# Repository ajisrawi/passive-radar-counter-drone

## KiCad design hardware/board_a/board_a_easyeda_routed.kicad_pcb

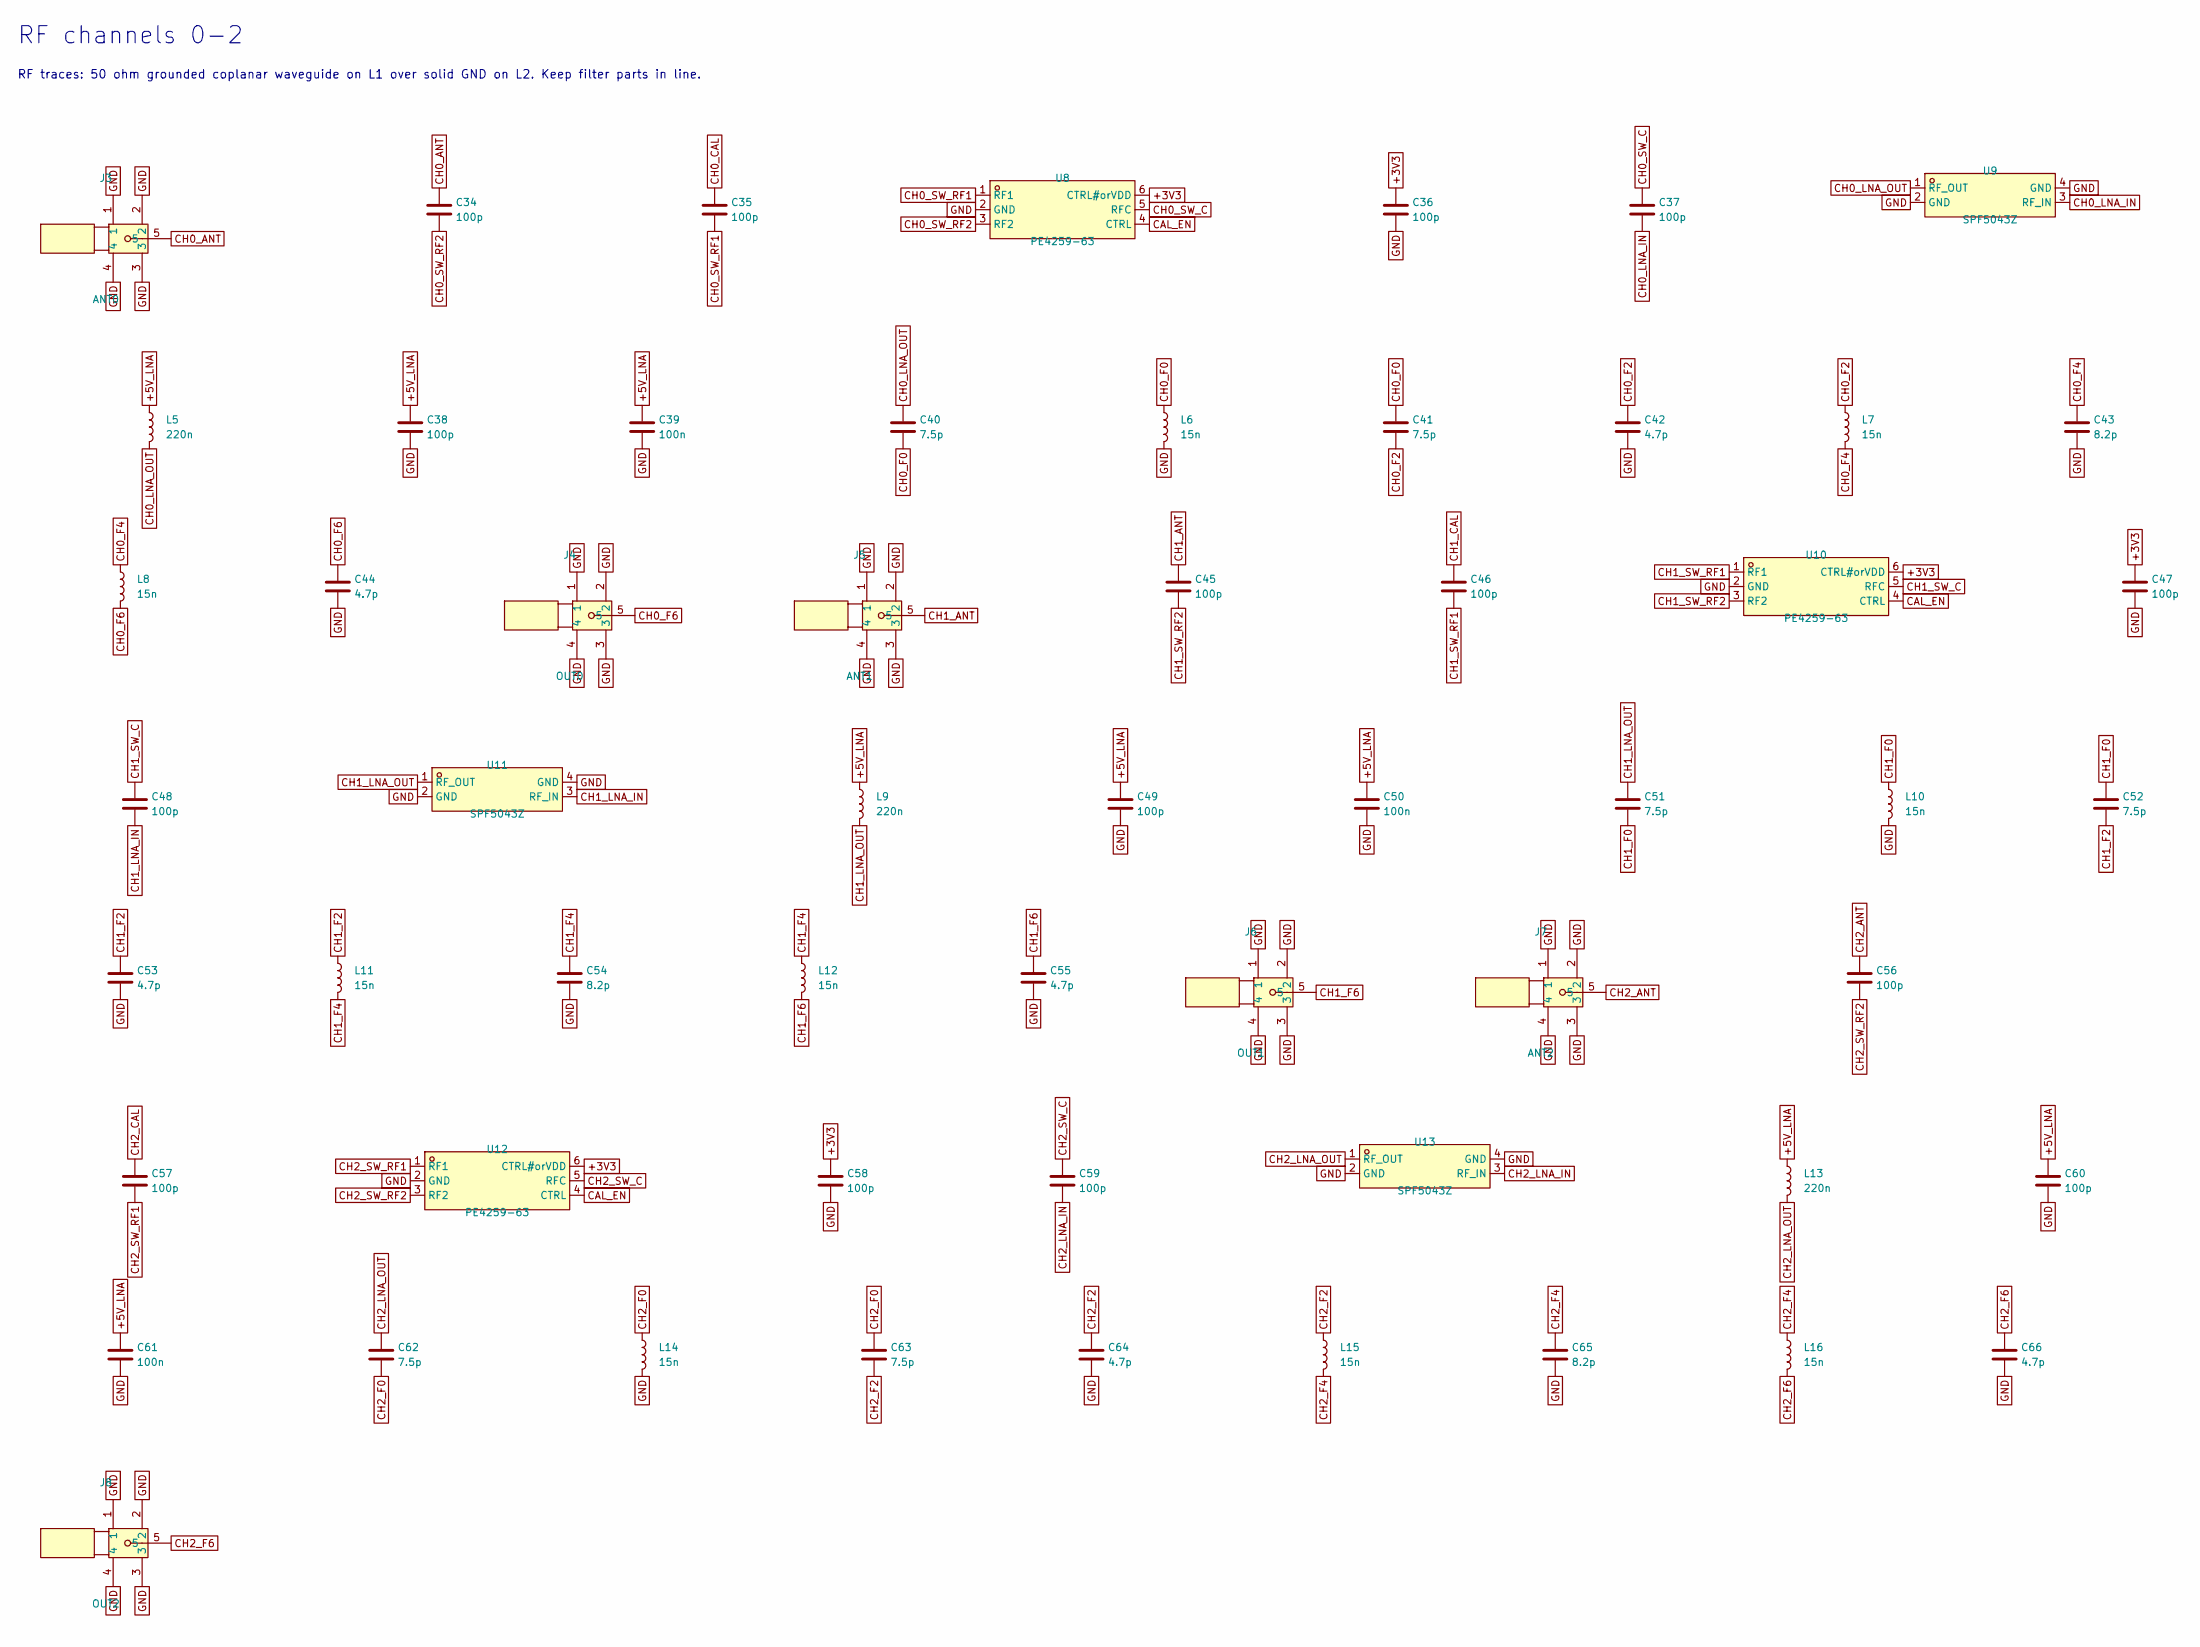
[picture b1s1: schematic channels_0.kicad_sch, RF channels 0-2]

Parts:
C34, C35, C36, C37, C38, C45, C46, C47, C48, C49, C56, C57, C58, C59, C60: 100p; C_0402_1005Metric
C39, C50, C61: 100n; C_0402_1005Metric; LCSC C1525
C40, C41, C51, C52, C62, C63: 7.5p; C_0402_1005Metric
C42, C44, C53, C55, C64, C66: 4.7p; C_0402_1005Metric
C43, C54, C65: 8.2p; C_0402_1005Metric
J3: ANT0; SMA-TH_BWSMA-KE-Z001; MPN BWSMA-KE-Z001; LCSC C496549
J4: OUT0; SMA-TH_BWSMA-KE-Z001; MPN BWSMA-KE-Z001; LCSC C496549
J5: ANT1; SMA-TH_BWSMA-KE-Z001; MPN BWSMA-KE-Z001; LCSC C496549
J6: OUT1; SMA-TH_BWSMA-KE-Z001; MPN BWSMA-KE-Z001; LCSC C496549
J7: ANT2; SMA-TH_BWSMA-KE-Z001; MPN BWSMA-KE-Z001; LCSC C496549
J8: OUT2; SMA-TH_BWSMA-KE-Z001; MPN BWSMA-KE-Z001; LCSC C496549
L5, L9, L13: 220n; L_0603_1608Metric
L6, L7, L8, L10, L11, L12, L14, L15, L16: 15n; L_0402_1005Metric
U8, U10, U12: PE4259-63; SC-70-6_L2.2-W1.3-P0.65-LS2.1-BL; MPN PE4259-63; LCSC C470892
U9, U11, U13: SPF5043Z; SOT343_L2.0-W1.3-P1.30-LS2.1-BL; MPN SPF5043Z; LCSC C470902

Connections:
+3V3: C36.1, C47.1, C58.1, U8.6 (CTRL#orVDD), U10.6 (CTRL#orVDD), U12.6 (CTRL#orVDD); also elsewhere on the board
+5V_LNA: C38.1, C39.1, C49.1, C50.1, C60.1, C61.1, L5.1, L9.1, L13.1; also elsewhere on the board
CAL_EN: U8.4 (CTRL), U10.4 (CTRL), U12.4 (CTRL); also elsewhere on the board
CH0_ANT: C34.1, J3.5
CH0_CAL: C35.1; also elsewhere on the board
CH0_F0: C40.2, C41.1, L6.1
CH0_F2: C41.2, C42.1, L7.1
CH0_F4: C43.1, L7.2, L8.1
CH0_F6: C44.1, J4.5, L8.2
CH0_LNA_IN: C37.2, U9.3 (RF_IN)
CH0_LNA_OUT: C40.1, L5.2, U9.1 (RF_OUT)
CH0_SW_C: C37.1, U8.5 (RFC)
CH0_SW_RF1: C35.2, U8.1 (RF1)
CH0_SW_RF2: C34.2, U8.3 (RF2)
CH1_ANT: C45.1, J5.5
CH1_CAL: C46.1; also elsewhere on the board
CH1_F0: C51.2, C52.1, L10.1
CH1_F2: C52.2, C53.1, L11.1
CH1_F4: C54.1, L11.2, L12.1
CH1_F6: C55.1, J6.5, L12.2
CH1_LNA_IN: C48.2, U11.3 (RF_IN)
CH1_LNA_OUT: C51.1, L9.2, U11.1 (RF_OUT)
CH1_SW_C: C48.1, U10.5 (RFC)
CH1_SW_RF1: C46.2, U10.1 (RF1)
CH1_SW_RF2: C45.2, U10.3 (RF2)
CH2_ANT: C56.1, J7.5
CH2_CAL: C57.1; also elsewhere on the board
CH2_F0: C62.2, C63.1, L14.1
CH2_F2: C63.2, C64.1, L15.1
CH2_F4: C65.1, L15.2, L16.1
CH2_F6: C66.1, J8.5, L16.2
CH2_LNA_IN: C59.2, U13.3 (RF_IN)
CH2_LNA_OUT: C62.1, L13.2, U13.1 (RF_OUT)
CH2_SW_C: C59.1, U12.5 (RFC)
CH2_SW_RF1: C57.2, U12.1 (RF1)
CH2_SW_RF2: C56.2, U12.3 (RF2)
GND: C36.2, C38.2, C39.2, C42.2, C43.2, C44.2, C47.2, C49.2, C50.2, C53.2, C54.2, C55.2, C58.2, C60.2, C61.2, C64.2, C65.2, C66.2, J3.1, J3.2, J3.3, J3.4, J4.1, J4.2, J4.3, J4.4, J5.1, J5.2, J5.3, J5.4, J6.1, J6.2, J6.3, J6.4, J7.1, J7.2, J7.3, J7.4, J8.1, J8.2, J8.3, J8.4, L6.2, L10.2, L14.2, U8.2 (GND), U9.2 (GND), U9.4 (GND), U10.2 (GND), U11.2 (GND), U11.4 (GND), U12.2 (GND), U13.2 (GND), U13.4 (GND); also elsewhere on the board

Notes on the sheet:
RF channels 0-2
RF traces: 50 ohm grounded coplanar waveguide on L1 over solid GND on L2. Keep filter parts in line.

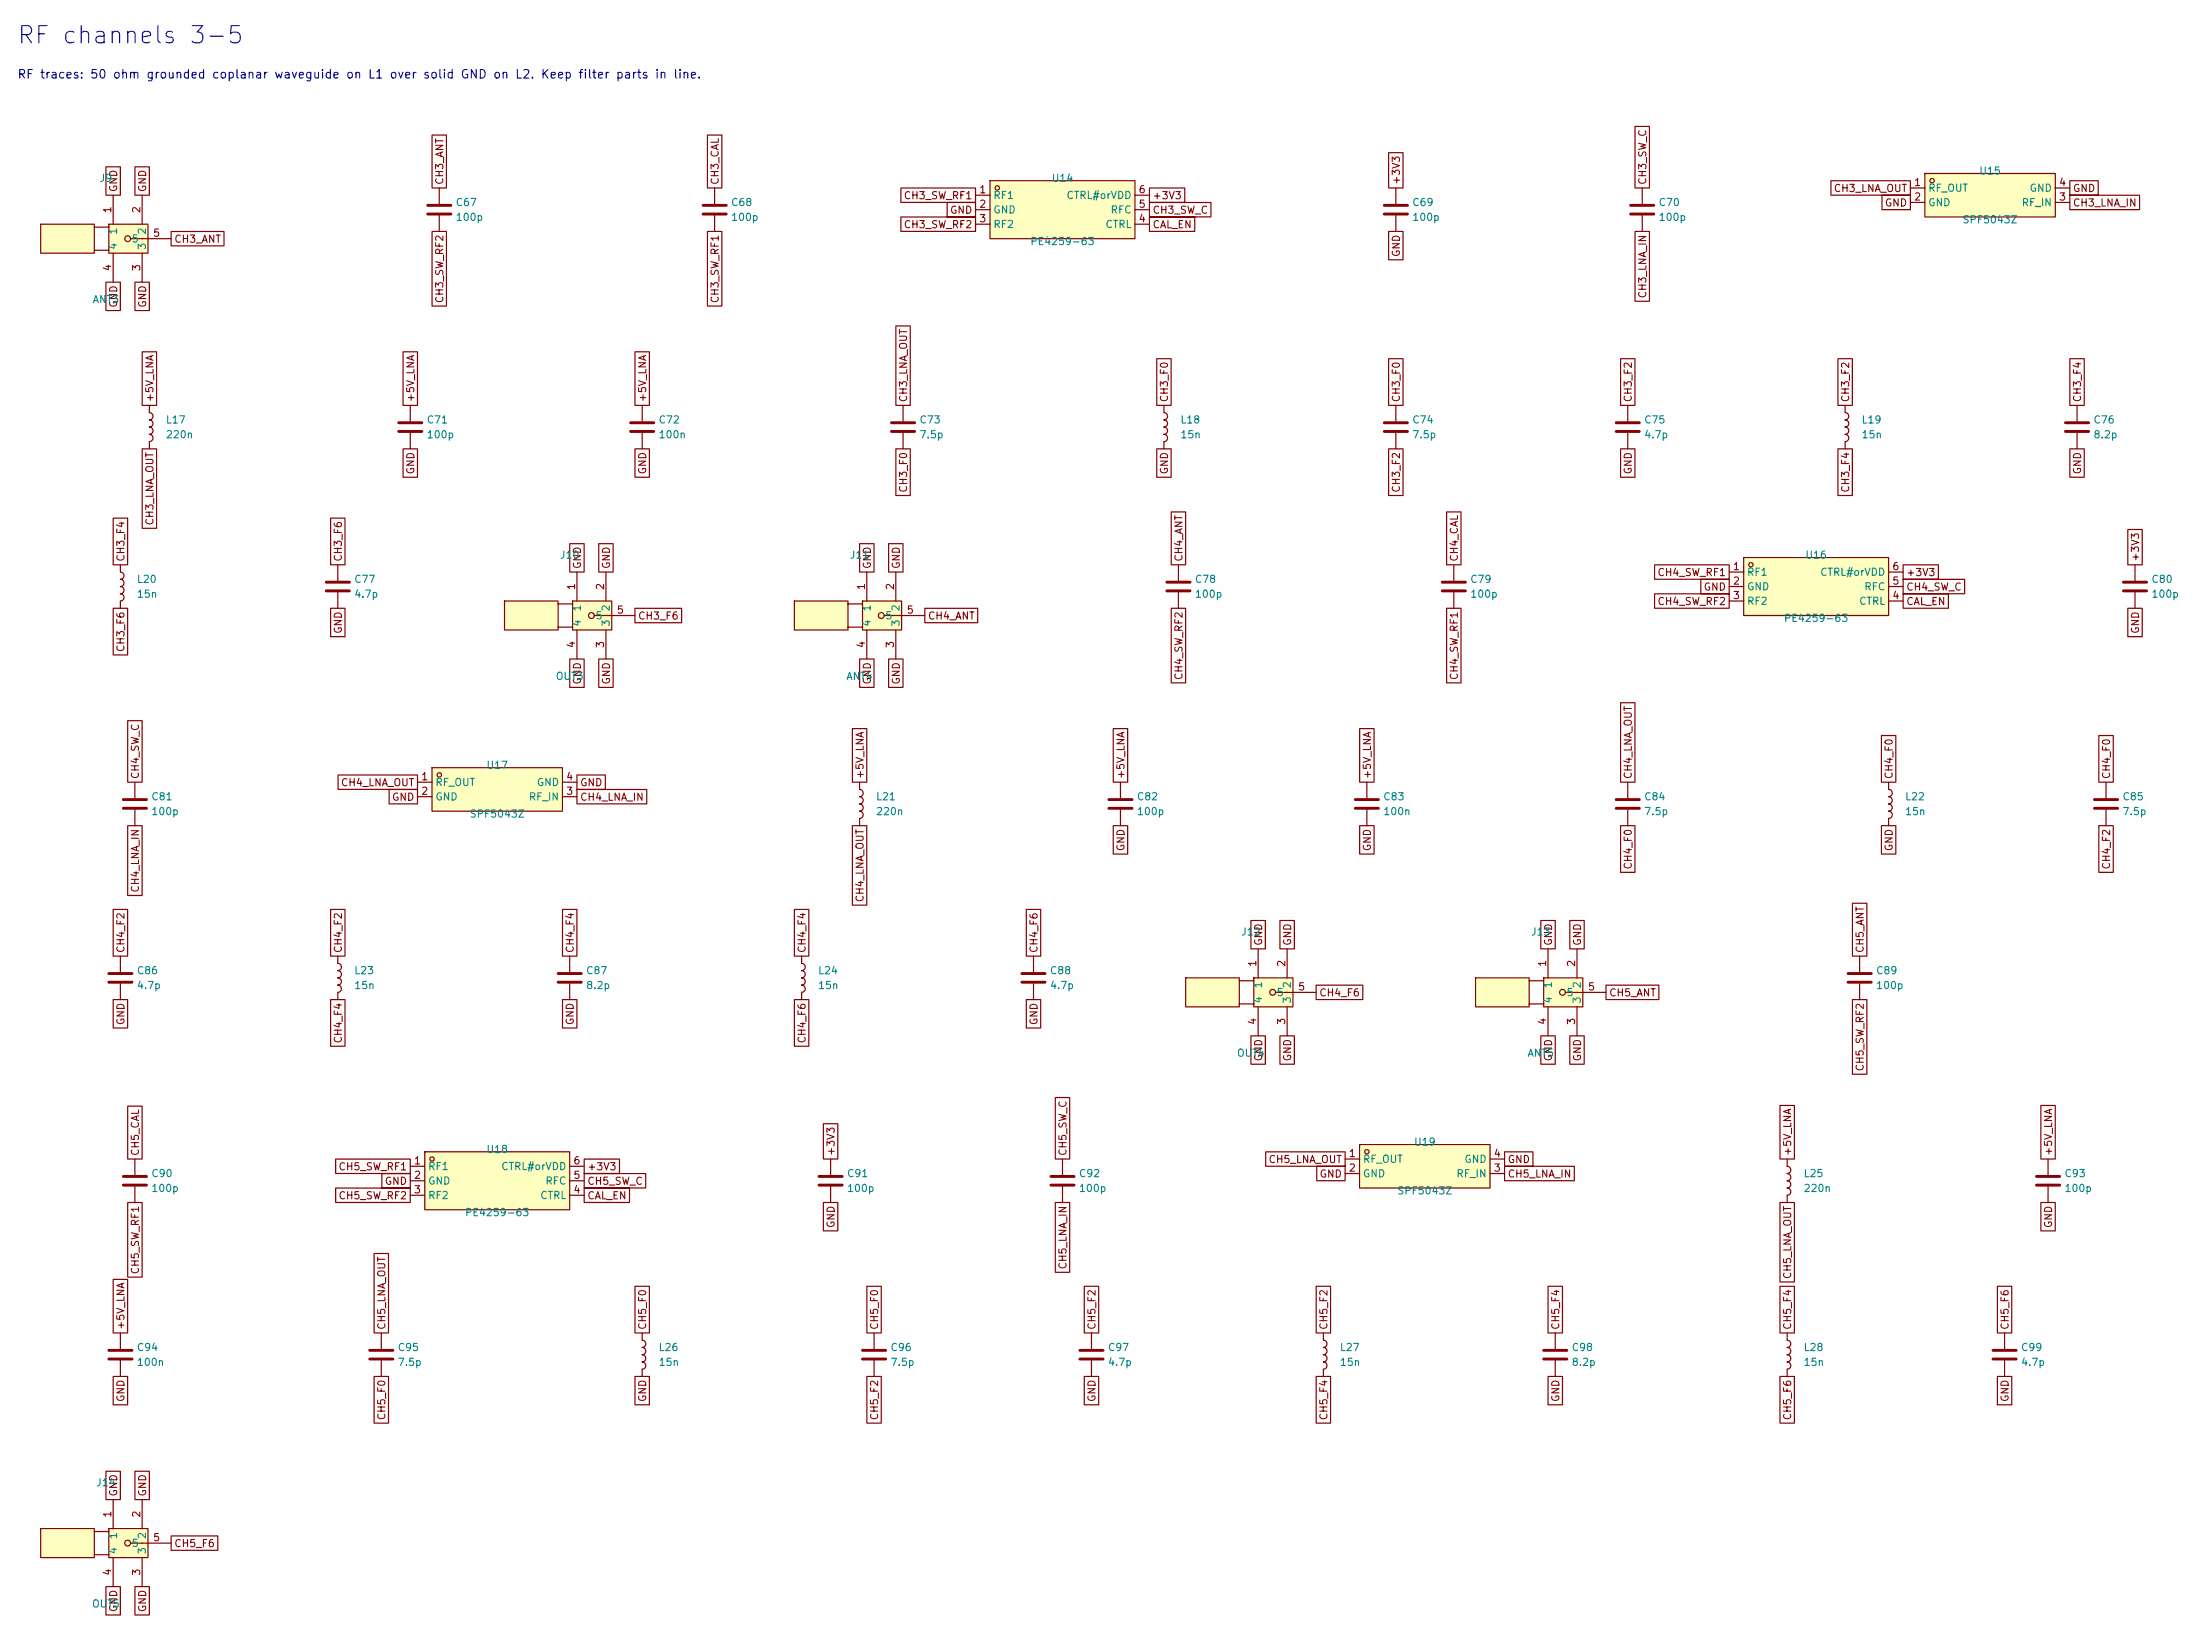
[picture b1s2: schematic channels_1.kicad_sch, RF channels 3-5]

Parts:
C67, C68, C69, C70, C71, C78, C79, C80, C81, C82, C89, C90, C91, C92, C93: 100p; C_0402_1005Metric
C72, C83, C94: 100n; C_0402_1005Metric; LCSC C1525
C73, C74, C84, C85, C95, C96: 7.5p; C_0402_1005Metric
C75, C77, C86, C88, C97, C99: 4.7p; C_0402_1005Metric
C76, C87, C98: 8.2p; C_0402_1005Metric
J9: ANT3; SMA-TH_BWSMA-KE-Z001; MPN BWSMA-KE-Z001; LCSC C496549
J10: OUT3; SMA-TH_BWSMA-KE-Z001; MPN BWSMA-KE-Z001; LCSC C496549
J11: ANT4; SMA-TH_BWSMA-KE-Z001; MPN BWSMA-KE-Z001; LCSC C496549
J12: OUT4; SMA-TH_BWSMA-KE-Z001; MPN BWSMA-KE-Z001; LCSC C496549
J13: ANT5; SMA-TH_BWSMA-KE-Z001; MPN BWSMA-KE-Z001; LCSC C496549
J14: OUT5; SMA-TH_BWSMA-KE-Z001; MPN BWSMA-KE-Z001; LCSC C496549
L17, L21, L25: 220n; L_0603_1608Metric
L18, L19, L20, L22, L23, L24, L26, L27, L28: 15n; L_0402_1005Metric
U14, U16, U18: PE4259-63; SC-70-6_L2.2-W1.3-P0.65-LS2.1-BL; MPN PE4259-63; LCSC C470892
U15, U17, U19: SPF5043Z; SOT343_L2.0-W1.3-P1.30-LS2.1-BL; MPN SPF5043Z; LCSC C470902

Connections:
+3V3: C69.1, C80.1, C91.1, U14.6 (CTRL#orVDD), U16.6 (CTRL#orVDD), U18.6 (CTRL#orVDD); also elsewhere on the board
+5V_LNA: C71.1, C72.1, C82.1, C83.1, C93.1, C94.1, L17.1, L21.1, L25.1; also elsewhere on the board
CAL_EN: U14.4 (CTRL), U16.4 (CTRL), U18.4 (CTRL); also elsewhere on the board
CH3_ANT: C67.1, J9.5
CH3_CAL: C68.1; also elsewhere on the board
CH3_F0: C73.2, C74.1, L18.1
CH3_F2: C74.2, C75.1, L19.1
CH3_F4: C76.1, L19.2, L20.1
CH3_F6: C77.1, J10.5, L20.2
CH3_LNA_IN: C70.2, U15.3 (RF_IN)
CH3_LNA_OUT: C73.1, L17.2, U15.1 (RF_OUT)
CH3_SW_C: C70.1, U14.5 (RFC)
CH3_SW_RF1: C68.2, U14.1 (RF1)
CH3_SW_RF2: C67.2, U14.3 (RF2)
CH4_ANT: C78.1, J11.5
CH4_CAL: C79.1; also elsewhere on the board
CH4_F0: C84.2, C85.1, L22.1
CH4_F2: C85.2, C86.1, L23.1
CH4_F4: C87.1, L23.2, L24.1
CH4_F6: C88.1, J12.5, L24.2
CH4_LNA_IN: C81.2, U17.3 (RF_IN)
CH4_LNA_OUT: C84.1, L21.2, U17.1 (RF_OUT)
CH4_SW_C: C81.1, U16.5 (RFC)
CH4_SW_RF1: C79.2, U16.1 (RF1)
CH4_SW_RF2: C78.2, U16.3 (RF2)
CH5_ANT: C89.1, J13.5
CH5_CAL: C90.1; also elsewhere on the board
CH5_F0: C95.2, C96.1, L26.1
CH5_F2: C96.2, C97.1, L27.1
CH5_F4: C98.1, L27.2, L28.1
CH5_F6: C99.1, J14.5, L28.2
CH5_LNA_IN: C92.2, U19.3 (RF_IN)
CH5_LNA_OUT: C95.1, L25.2, U19.1 (RF_OUT)
CH5_SW_C: C92.1, U18.5 (RFC)
CH5_SW_RF1: C90.2, U18.1 (RF1)
CH5_SW_RF2: C89.2, U18.3 (RF2)
GND: C69.2, C71.2, C72.2, C75.2, C76.2, C77.2, C80.2, C82.2, C83.2, C86.2, C87.2, C88.2, C91.2, C93.2, C94.2, C97.2, C98.2, C99.2, J9.1, J9.2, J9.3, J9.4, J10.1, J10.2, J10.3, J10.4, J11.1, J11.2, J11.3, J11.4, J12.1, J12.2, J12.3, J12.4, J13.1, J13.2, J13.3, J13.4, J14.1, J14.2, J14.3, J14.4, L18.2, L22.2, L26.2, U14.2 (GND), U15.2 (GND), U15.4 (GND), U16.2 (GND), U17.2 (GND), U17.4 (GND), U18.2 (GND), U19.2 (GND), U19.4 (GND); also elsewhere on the board

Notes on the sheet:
RF channels 3-5
RF traces: 50 ohm grounded coplanar waveguide on L1 over solid GND on L2. Keep filter parts in line.

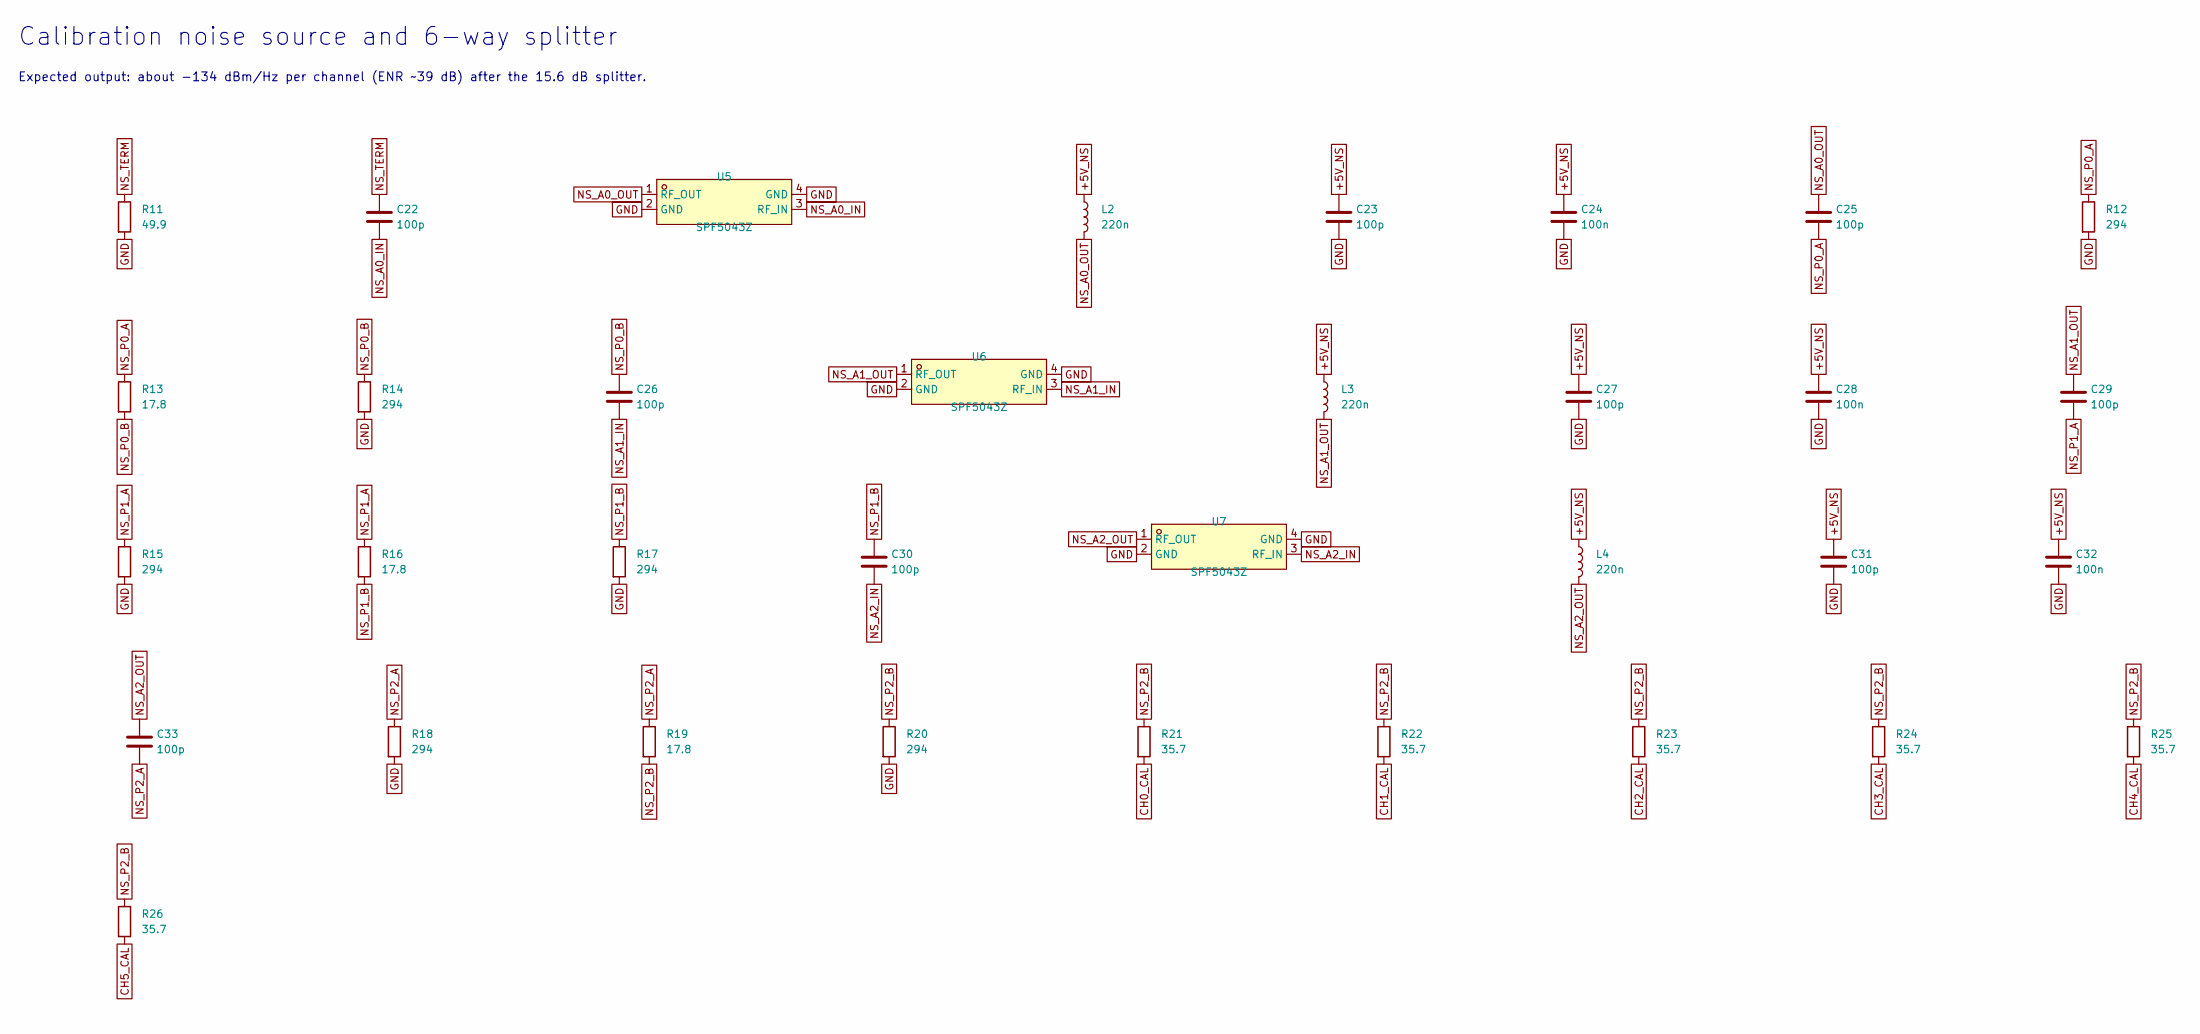
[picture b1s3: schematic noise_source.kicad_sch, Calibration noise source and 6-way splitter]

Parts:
C22, C23, C25, C26, C27, C29, C30, C31, C33: 100p; C_0402_1005Metric
C24, C28, C32: 100n; C_0402_1005Metric; LCSC C1525
L2, L3, L4: 220n; L_0603_1608Metric
R11: 49.9; R_0402_1005Metric
R12, R14, R15, R17, R18, R20: 294; R_0402_1005Metric
R13, R16, R19: 17.8; R_0402_1005Metric
R21, R22, R23, R24, R25, R26: 35.7; R_0402_1005Metric
U5, U6, U7: SPF5043Z; SOT343_L2.0-W1.3-P1.30-LS2.1-BL; MPN SPF5043Z; LCSC C470902

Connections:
+5V_NS: C23.1, C24.1, C27.1, C28.1, C31.1, C32.1, L2.1, L3.1, L4.1; also elsewhere on the board
CH0_CAL: R21.2; also elsewhere on the board
CH1_CAL: R22.2; also elsewhere on the board
CH2_CAL: R23.2; also elsewhere on the board
CH3_CAL: R24.2; also elsewhere on the board
CH4_CAL: R25.2; also elsewhere on the board
CH5_CAL: R26.2; also elsewhere on the board
GND: C23.2, C24.2, C27.2, C28.2, C31.2, C32.2, R11.2, R12.2, R14.2, R15.2, R17.2, R18.2, R20.2, U5.2 (GND), U5.4 (GND), U6.2 (GND), U6.4 (GND), U7.2 (GND), U7.4 (GND); also elsewhere on the board
NS_A0_IN: C22.2, U5.3 (RF_IN)
NS_A0_OUT: C25.1, L2.2, U5.1 (RF_OUT)
NS_A1_IN: C26.2, U6.3 (RF_IN)
NS_A1_OUT: C29.1, L3.2, U6.1 (RF_OUT)
NS_A2_IN: C30.2, U7.3 (RF_IN)
NS_A2_OUT: C33.1, L4.2, U7.1 (RF_OUT)
NS_P0_A: C25.2, R12.1, R13.1
NS_P0_B: C26.1, R13.2, R14.1
NS_P1_A: C29.2, R15.1, R16.1
NS_P1_B: C30.1, R16.2, R17.1
NS_P2_A: C33.2, R18.1, R19.1
NS_P2_B: R19.2, R20.1, R21.1, R22.1, R23.1, R24.1, R25.1, R26.1
NS_TERM: C22.1, R11.1

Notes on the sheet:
Calibration noise source and 6-way splitter
Expected output: about -134 dBm/Hz per channel (ENR ~39 dB) after the 15.6 dB splitter.

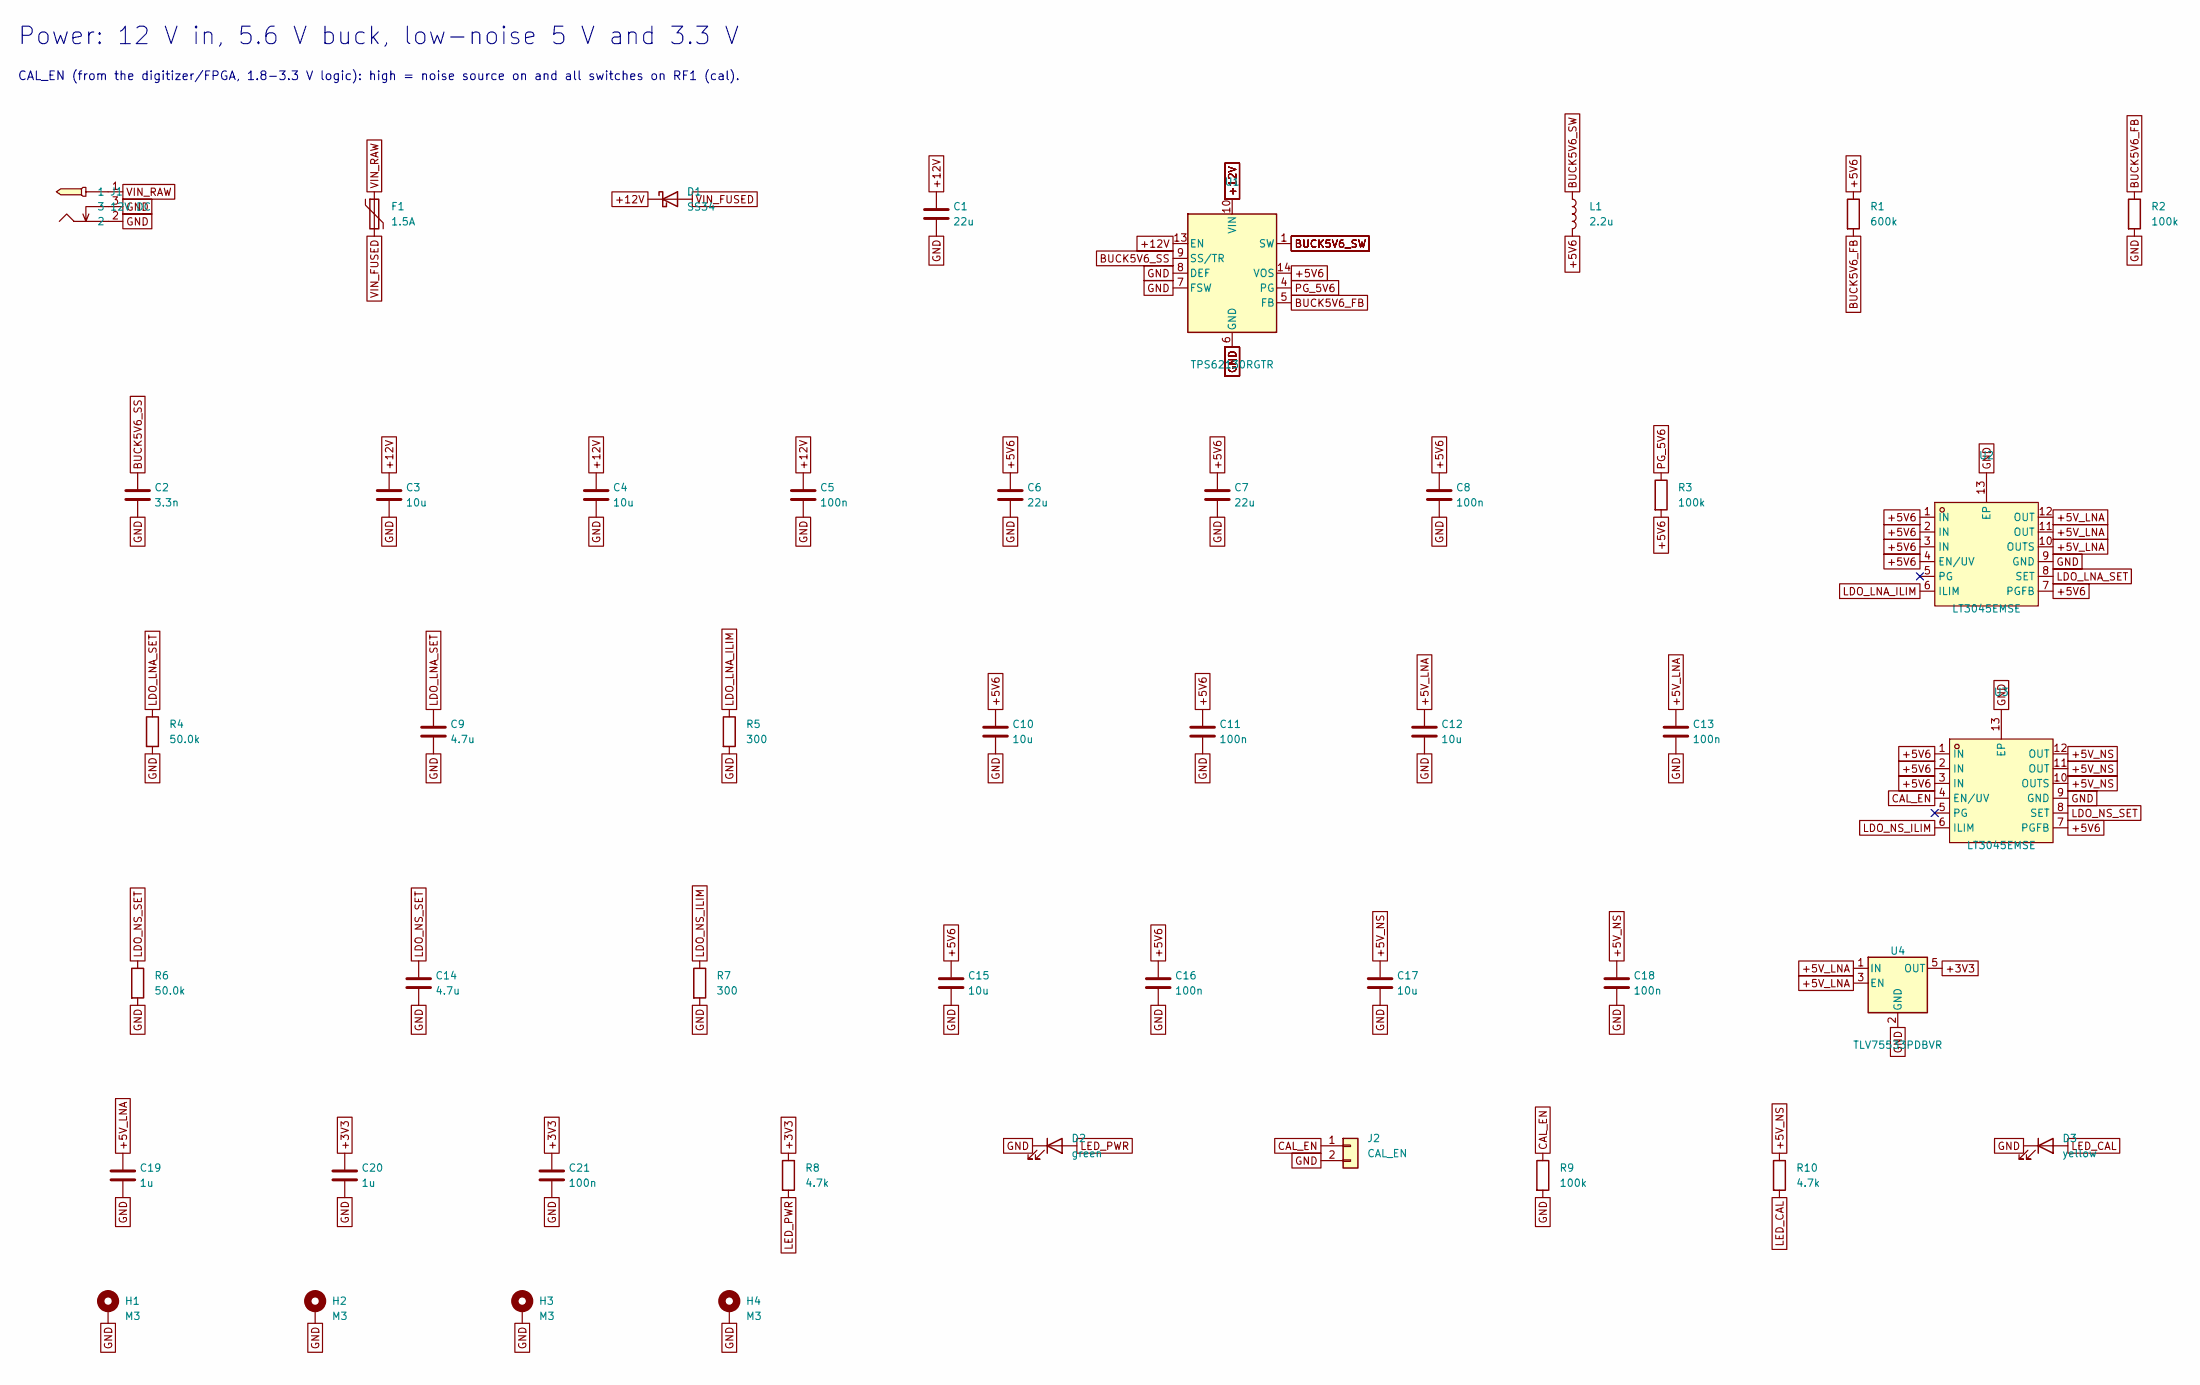
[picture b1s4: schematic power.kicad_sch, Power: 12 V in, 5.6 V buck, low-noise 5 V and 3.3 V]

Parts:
C1: 22u; C_1206_3216Metric
C2: 3.3n; C_0402_1005Metric
C3, C4: 10u; C_0805_2012Metric
C5, C8, C11, C13, C16, C18, C21: 100n; C_0402_1005Metric; LCSC C1525
C6, C7: 22u; C_0805_2012Metric; LCSC C45783
C9, C14: 4.7u; C_0603_1608Metric
C10, C12, C15, C17: 10u; C_0603_1608Metric; LCSC C19702
C19, C20: 1u; C_0402_1005Metric; LCSC C52923
D1: SS34; D_SMA; MPN SS34; LCSC C8678
D2: green; LED_0603_1608Metric
D3: yellow; LED_0603_1608Metric
F1: 1.5A; Fuse_1206_3216Metric
H1, H2, H3, H4: M3; MountingHole_3.2mm_M3_Pad_Via
J1: 12V DC; DC-IN-TH_DC-005C-20A; MPN DC-005C-20A; LCSC C84007
J2: CAL_EN; PinHeader_1x02_P2.54mm_Vertical
L1: 2.2u; L_Bourns-SRN4018; MPN SRN4018-2R2M
R1: 600k; R_0402_1005Metric
R2, R3, R9: 100k; R_0402_1005Metric; LCSC C25741
R4, R6: 50.0k; R_0402_1005Metric; Tolerance 0.1%
R5, R7: 300; R_0402_1005Metric
R8, R10: 4.7k; R_0402_1005Metric; LCSC C25900
U1: TPS62130RGTR; VQFN-16-1EP_3x3mm_P0.5mm_EP1.68x1.68mm; MPN TPS62130RGTR; LCSC C43590
U2, U3: LT3045EMSE; MSOP-12_L4.0-W3.0-P0.65-LS4.9-BL-EP; MPN LT3045EMSE#PBF; LCSC C580012
U4: TLV75533PDBVR; SOT-23-5; LCSC C404027

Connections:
+3V3: C20.1, C21.1, R8.1, U4.5 (OUT); also elsewhere on the board
+5V6: C6.1, C7.1, C8.1, C10.1, C11.1, C15.1, C16.1, L1.2, R1.1, R3.2, U1.14 (VOS), U2.1 (IN), U2.2 (IN), U2.3 (IN), U2.4 (EN/UV), U2.7 (PGFB), U3.1 (IN), U3.2 (IN), U3.3 (IN), U3.7 (PGFB)
+5V_LNA: C12.1, C13.1, C19.1, U2.10 (OUTS), U2.11 (OUT), U2.12 (OUT), U4.1 (IN), U4.3 (EN); also elsewhere on the board
+5V_NS: C17.1, C18.1, R10.1, U3.10 (OUTS), U3.11 (OUT), U3.12 (OUT); also elsewhere on the board
+12V: C1.1, C3.1, C4.1, C5.1, D1.1 (K), U1.10 (VIN), U1.11 (VIN), U1.12 (VIN), U1.13 (EN)
BUCK5V6_FB: R1.2, R2.1, U1.5 (FB)
BUCK5V6_SS: C2.1, U1.9 (SS/TR)
BUCK5V6_SW: L1.1, U1.1 (SW), U1.2 (SW), U1.3 (SW)
CAL_EN: J2.1, R9.1, U3.4 (EN/UV); also elsewhere on the board
GND: C1.2, C2.2, C3.2, C4.2, C5.2, C6.2, C7.2, C8.2, C9.2, C10.2, C11.2, C12.2, C13.2, C14.2, C15.2, C16.2, C17.2, C18.2, C19.2, C20.2, C21.2, D2.1 (K), D3.1 (K), H1.1, H2.1, H3.1, H4.1, J1.2, J1.3, J2.2, R2.2, R4.2, R5.2, R6.2, R7.2, R9.2, U1.6 (GND), U1.7 (FSW), U1.8 (DEF), U1.15 (GND), U1.16 (GND), U1.17 (GND), U2.9 (GND), U2.13 (EP), U3.9 (GND), U3.13 (EP), U4.2 (GND); also elsewhere on the board
LDO_LNA_ILIM: R5.1, U2.6 (ILIM)
LDO_LNA_SET: C9.1, R4.1, U2.8 (SET)
LDO_NS_ILIM: R7.1, U3.6 (ILIM)
LDO_NS_SET: C14.1, R6.1, U3.8 (SET)
LED_CAL: D3.2 (A), R10.2
LED_PWR: D2.2 (A), R8.2
PG_5V6: R3.1, U1.4 (PG)
VIN_FUSED: D1.2 (A), F1.2
VIN_RAW: F1.1, J1.1

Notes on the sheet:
Power: 12 V in, 5.6 V buck, low-noise 5 V and 3.3 V
CAL_EN (from the digitizer/FPGA, 1.8-3.3 V logic): high = noise source on and all switches on RF1 (cal).

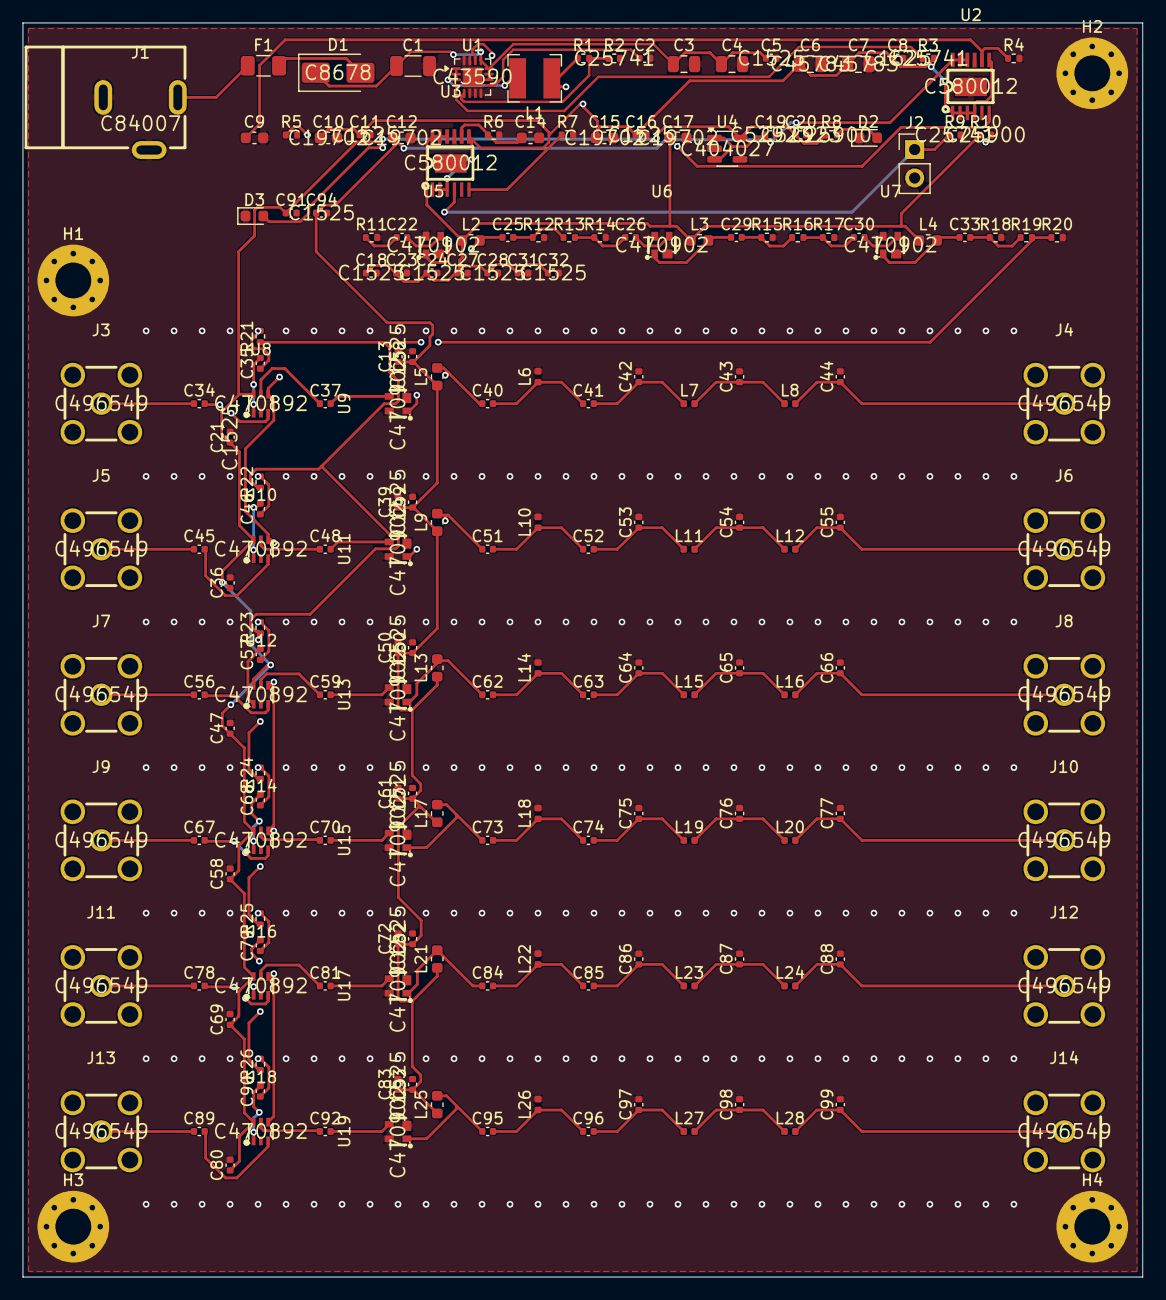
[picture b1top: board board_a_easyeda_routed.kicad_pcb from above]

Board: 4 copper layers, 100.0 x 112.0 mm, 194 parts (0 on the bottom side), 98 nets.
